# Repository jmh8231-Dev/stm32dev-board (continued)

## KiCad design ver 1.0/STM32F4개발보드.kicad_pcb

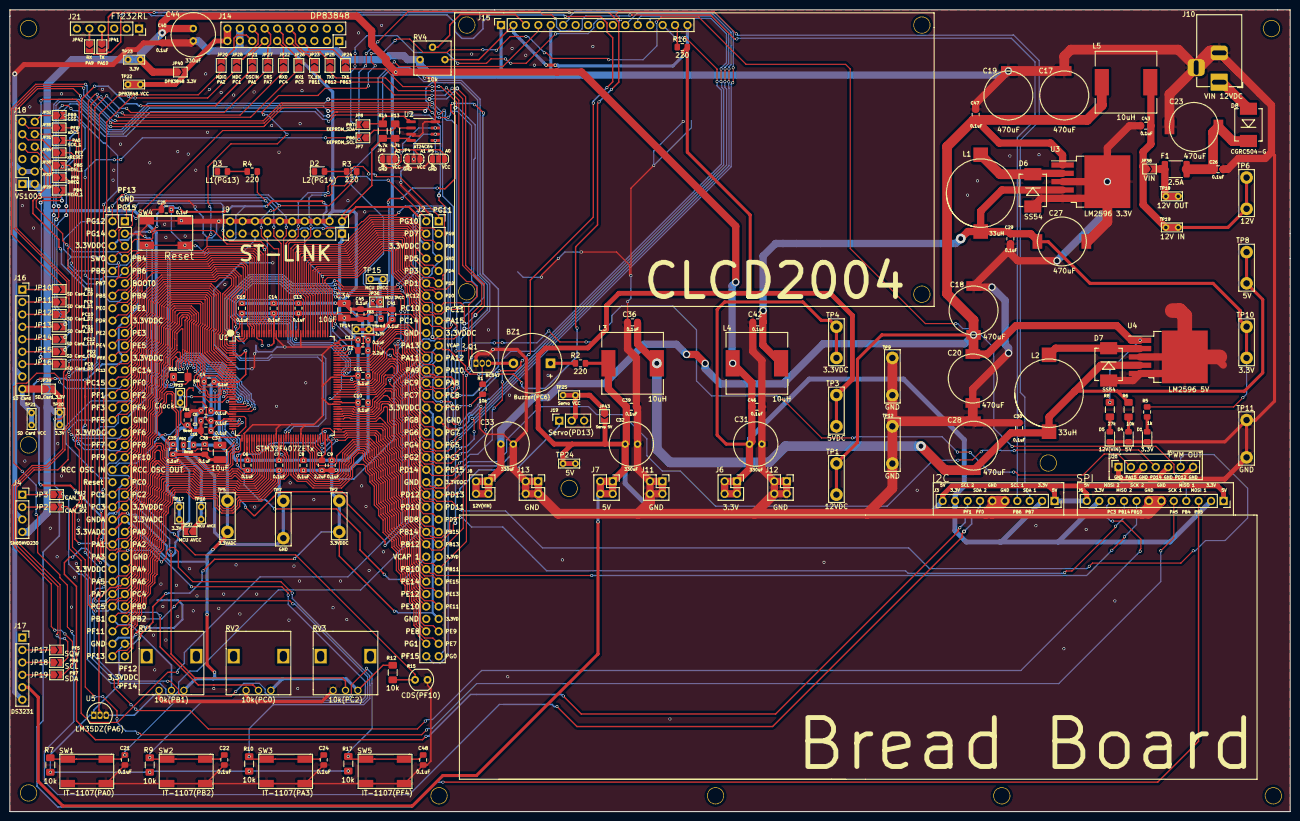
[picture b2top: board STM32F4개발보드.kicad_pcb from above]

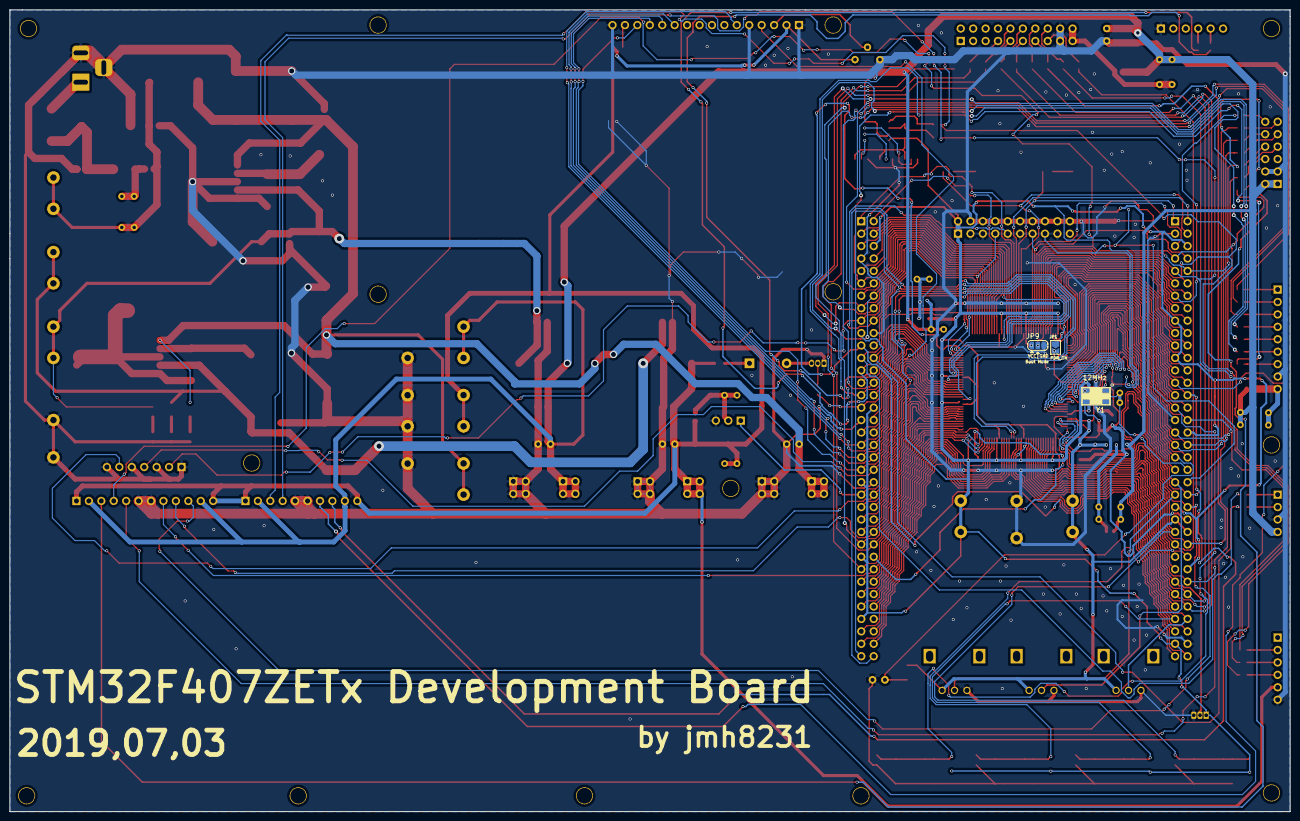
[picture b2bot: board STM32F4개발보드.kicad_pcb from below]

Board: 2 copper layers, 261.6 x 163.8 mm, 202 parts (3 on the bottom side), 182 nets.

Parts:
 : h
 #2,  #3,  #4,  #5,  #6,  #7,  #8,  #9,  #10,  #11,  #12,  #13,  #14: h
BZ1: Buzzer(PC6); Buzzer_12x9.5RM7.6
C1, C2: 2.2uF; C_0805_2012Metric_Pad1.15x1.40mm_HandSolder
C3, C4, C5, C6, C7, C8, C9, C10, C11, C12, C13, C14, C15, C16, C21, C22, C24, C25, C26, C29, C30, C35, C36, C38, C39, C40, C41, C42, C43, C45, C46, C47, C48: 0.1uF; C_0805_2012Metric_Pad1.15x1.40mm_HandSolder
C17, C18, C19, C20, C23, C27, C28: 470uF; MVG25WV470M
C31, C32, C33, C44: 330uF; c1
C34, C37: 10uF; C_1210_3225Metric_Pad1.42x2.65mm_HandSolder
D1: 3.3V; LED_0805_2012Metric_Pad1.15x1.40mm_HandSolder
D2: L2(PG14); LED_0805_2012Metric_Pad1.15x1.40mm_HandSolder
D3: L1(PG13); LED_0805_2012Metric_Pad1.15x1.40mm_HandSolder
D4: 5V; LED_0805_2012Metric_Pad1.15x1.40mm_HandSolder
D5: 12V(VIN); LED_0805_2012Metric_Pad1.15x1.40mm_HandSolder
D6, D7: SS54
D8: CGRC504-G; SS54
F1: 2.5A; Fuse_1812_4532Metric_Pad1.30x3.40mm_HandSolder
FB1, FB2, FB3: Bead; L_0805_2012Metric_Pad1.15x1.40mm_HandSolder
J1, J2: PinSocket_2x36_P2.54mm_Vertical
J3: I2C; PinSocket_1x10_P2.54mm_Vertical
J4: SN65HVD230; PinSocket_1x04_P2.54mm_Vertical
J5: SPI; PinSocket_1x12_P2.54mm_Vertical
J6: 3.3V; PinSocket_2x02_P2.54mm_Vertical
J7: 5V; PinSocket_2x02_P2.54mm_Vertical
J8: 12V(VIN); PinSocket_2x02_P2.54mm_Vertical
J9: ST-LINK; PinSocket_2x10_P2.54mm_Vertical
J10: VIN 12VDC; BarrelJack_Horizontal
J11, J12, J13: GND; PinSocket_2x02_P2.54mm_Vertical
J14: DP83848; PinSocket_2x10_P2.54mm_Vertical
J15: CLCD2004; PinSocket_1x16_P2.54mm_Vertical
J16: SD Card; PinSocket_1x09_P2.54mm_Vertical
J17: DS3231; PinSocket_1x06_P2.54mm_Vertical
J18: VS1003; PinSocket_2x06_P2.54mm_Vertical
J19: Servo(PD13); PinSocket_1x03_P2.54mm_Vertical
J20: PWM OUT; PinSocket_1x07_P2.54mm_Vertical
J21: FT232RL; PinSocket_1x06_P2.54mm_Vertical
JP1: PDR_ON; SolderJumper-2_P1.3mm_Open_TrianglePad1.0x1.5mm
JP2: CAN_RX; SolderJumper-2_P1.3mm_Open_TrianglePad1.0x1.5mm
JP3: CAN_TX; SolderJumper-2_P1.3mm_Open_TrianglePad1.0x1.5mm
JP4: A1; SolderJumper-3_P1.3mm_Open_RoundedPad1.0x1.5mm
JP5: A0; SolderJumper-3_P1.3mm_Open_RoundedPad1.0x1.5mm
JP6: A2; SolderJumper-3_P1.3mm_Open_RoundedPad1.0x1.5mm
JP7: EEPROM_SCL; SolderJumper-2_P1.3mm_Open_TrianglePad1.0x1.5mm
JP8: EEPROM_SDA; SolderJumper-2_P1.3mm_Open_TrianglePad1.0x1.5mm
JP9: Boot Mode; SolderJumper-3_P1.3mm_Open_RoundedPad1.0x1.5mm
JP10: SD Card_CD; SolderJumper-2_P1.3mm_Open_TrianglePad1.0x1.5mm
JP11: SD Card_D1; SolderJumper-2_P1.3mm_Open_TrianglePad1.0x1.5mm
JP12: SD Card_D2; SolderJumper-2_P1.3mm_Open_TrianglePad1.0x1.5mm
JP13: SD Card_D3; SolderJumper-2_P1.3mm_Open_TrianglePad1.0x1.5mm
JP14: SD Card_CLK; SolderJumper-2_P1.3mm_Open_TrianglePad1.0x1.5mm
JP15: SD Card_CMD; SolderJumper-2_P1.3mm_Open_TrianglePad1.0x1.5mm
JP16: SD Card_D0; SolderJumper-2_P1.3mm_Open_TrianglePad1.0x1.5mm
JP17: SQW; SolderJumper-2_P1.3mm_Open_TrianglePad1.0x1.5mm
JP18: SCL; SolderJumper-2_P1.3mm_Open_TrianglePad1.0x1.5mm
JP19: SDA; SolderJumper-2_P1.3mm_Open_TrianglePad1.0x1.5mm
JP20: MDIO; SolderJumper-2_P1.3mm_Open_TrianglePad1.0x1.5mm
JP21: OSCIN; SolderJumper-2_P1.3mm_Open_TrianglePad1.0x1.5mm
JP22: RX0; SolderJumper-2_P1.3mm_Open_TrianglePad1.0x1.5mm
JP23: TX_EN; SolderJumper-2_P1.3mm_Open_TrianglePad1.0x1.5mm
JP24: TX1; SolderJumper-2_P1.3mm_Open_TrianglePad1.0x1.5mm
JP25: TX0; SolderJumper-2_P1.3mm_Open_TrianglePad1.0x1.5mm
JP26: RX1; SolderJumper-2_P1.3mm_Open_TrianglePad1.0x1.5mm
JP27: CRS; SolderJumper-2_P1.3mm_Open_TrianglePad1.0x1.5mm
JP28: MDC; SolderJumper-2_P1.3mm_Open_TrianglePad1.0x1.5mm
JP29: MISO_1; SolderJumper-2_P1.3mm_Open_TrianglePad1.0x1.5mm
JP30: MOSI_1; SolderJumper-2_P1.3mm_Open_TrianglePad1.0x1.5mm
JP31: SCK_1; SolderJumper-2_P1.3mm_Open_TrianglePad1.0x1.5mm
JP32: CSS; SolderJumper-2_P1.3mm_Open_TrianglePad1.0x1.5mm
JP33: DREQ; SolderJumper-2_P1.3mm_Open_TrianglePad1.0x1.5mm
JP34: xRESET; SolderJumper-2_P1.3mm_Open_TrianglePad1.0x1.5mm
JP35: xDCS; SolderJumper-2_P1.3mm_Open_TrianglePad1.0x1.5mm
JP36: MCU DVCC; SolderJumper-2_P1.3mm_Open_TrianglePad1.0x1.5mm
JP37: MCU AVCC; SolderJumper-2_P1.3mm_Open_TrianglePad1.0x1.5mm
JP38: VIN; SolderJumper-2_P1.3mm_Open_TrianglePad1.0x1.5mm
JP39: SD_Card_3.3V; SolderJumper-2_P1.3mm_Open_TrianglePad1.0x1.5mm
JP40: DP83848 3.3V; SolderJumper-2_P1.3mm_Open_TrianglePad1.0x1.5mm
JP41: TX; SolderJumper-2_P1.3mm_Open_TrianglePad1.0x1.5mm
JP42: RX; SolderJumper-2_P1.3mm_Open_TrianglePad1.0x1.5mm
JP43: Servo 5V; SolderJumper-2_P1.3mm_Open_TrianglePad1.0x1.5mm
L1, L2: 33uH; SRR1806-330M
L3, L4, L5: 10uH; L_12x12mm_H6mm
Q1: BC547; TO-92_Inline
R1: 10k; R_0805_2012Metric_Pad1.15x1.40mm_HandSolder
R2, R3, R4, R16: 220; R_0805_2012Metric_Pad1.15x1.40mm_HandSolder
R5: 1k; R_0805_2012Metric_Pad1.15x1.40mm_HandSolder
R6, R7, R9, R10, R11, R12, R17: 10k; R_1206_3216Metric_Pad1.42x1.75mm_HandSolder
R8: 27k; R_1206_3216Metric_Pad1.42x1.75mm_HandSolder
R13, R14: 4.7k; R_1206_3216Metric_Pad1.42x1.75mm_HandSolder
R15: CDS(PF10); R_LDR_4.9x4.2mm_P2.54mm_Vertical
RV1: 10k(PB1); RV09H20SQ-B10K
RV2: 10k(PC0); RV09H20SQ-B10K
RV3: 10k(PC2); RV09H20SQ-B10K
RV4: 10k; 3362P-103LF
SW1: IT-1107(PA0); SW_SMD_IT-1107
SW2: IT-1107(PB2); SW_SMD_IT-1107
SW3: IT-1107(PA3); SW_SMD_IT-1107
SW4: Reset; SW_SMD_IT-1107
SW5: IT-1107(PF4); SW_SMD_IT-1107
TP1: 12VDC; TestPoint_Bridge_Pitch6.35mm_Drill1.3mm
TP2: 3.3VDDC; TestPoint_Bridge_Pitch6.35mm_Drill1.3mm
TP3: 5VDC; TestPoint_Bridge_Pitch6.35mm_Drill1.3mm
TP4: 3.3VDC; TestPoint_Bridge_Pitch6.35mm_Drill1.3mm
TP5: 3.3VADC; TestPoint_Bridge_Pitch6.35mm_Drill1.3mm
TP6: 12V; TestPoint_Bridge_Pitch6.35mm_Drill1.3mm
TP7, TP9, TP11, TP12: GND; TestPoint_Bridge_Pitch7.62mm_Drill1.3mm
TP8: 5V; TestPoint_Bridge_Pitch6.35mm_Drill1.3mm
TP10: 3.3V; TestPoint_Bridge_Pitch6.35mm_Drill1.3mm
TP13: Clock; TestPoint_Bridge_Pitch2.0mm_Drill0.7mm
TP14, TP17, TP20, TP23: 3.3V; TestPoint_Bridge_Pitch2.54mm_Drill0.7mm
TP15: MCU DVCC; TestPoint_Bridge_Pitch2.54mm_Drill0.7mm
TP16: MCU AVCC; TestPoint_Bridge_Pitch2.54mm_Drill0.7mm
TP18: 12V OUT; TestPoint_Bridge_Pitch2.54mm_Drill0.7mm
TP19: 12V IN; TestPoint_Bridge_Pitch2.54mm_Drill0.7mm
TP21: SD Card VCC; TestPoint_Bridge_Pitch2.54mm_Drill0.7mm
TP22: DP83848 VCC; TestPoint_Bridge_Pitch2.54mm_Drill0.7mm
TP24: 5V; TestPoint_Bridge_Pitch2.54mm_Drill0.7mm
TP25: Servo VCC; TestPoint_Bridge_Pitch2.54mm_Drill0.7mm
U1: STM32F407ZETx; LQFP-144_20x20mm_P0.5mm
U2: AT24C64; SOIC-8_3.9x4.9mm_P1.27mm
U3: LM2596 3.3V; TO-263-5_TabPin3
U4: LM2596 5V; TO-263-5_TabPin3
U5: LM35DZ(PA6); TO-92L_Inline
Y1: 12MHz; FT5HNBPK12.0-T1

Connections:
3.3VADC: C3.1, C16.2, C37.1, C38.1, FB2.1, J1.49, J1.52, R12.2, RV1.3, RV2.3, RV3.3, TP5.1, U1.32, U1.33, Y1.4
3.3VDDC: C4.2, C5.2, C6.2, C7.2, C8.2, C9.2, C10.2, C11.2, C12.2, C13.2, C14.2, C15.2, C34.1, C45.1, FB3.1, J1.6, J1.17, J1.18, J1.23, J1.36, J1.47, J1.58, J1.69, J2.6, J2.19, J2.32, J2.43, J2.55, J2.65, J9.1, J9.2, JP1.2, JP4.3, JP5.3, JP6.3, JP9.1, R7.1, R9.1, R10.1, R11.1, R13.2, R14.2, R17.1, TP2.1, U1.6, U1.17, U1.30, U1.39, U1.52, U1.62, U1.72, U1.84, U1.95, U1.108, U1.121, U1.131, U1.143, U1.144, U2.8, U5.1
3.3VOUT: C31.2, C35.1, C40.2, C41.1, C44.2, C46.1, J3.2, J3.9, J4.4, J5.2, J5.11, J6.1, J6.2, J6.3, J6.4, J18.1, J18.2, JP36.2, JP37.2, JP39.2, JP40.1, L4.2, TP4.1, TP14.1, TP17.1, TP20.1, TP23.1
5VOUT: C32.1, C39.1, J3.1, J3.10, J5.1, J5.12, J7.1, J7.2, J7.3, J7.4, J15.2, J17.5, JP43.2, L3.2, R2.2, R16.2, RV4.3, TP3.1, TP24.1
12V: F1.1, JP38.2, TP18.1
12VOUT: C17.1, C18.1, C19.1, C20.1, C33.1, C47.1, J8.1, J8.2, J8.3, J8.4, L5.2, R8.2, TP1.1, U3.1, U4.1
+3V3: C27.1, C29.1, C42.1, L1.2, L4.1, R5.2, TP10.1, U3.4
+5V: C28.1, C30.1, C36.1, L2.2, L3.1, R6.2, TP8.1, U4.4
+12V: C43.1, JP38.1, L5.1, TP6.1, TP19.1
A: J15.15, R16.1
A0: JP5.2, U2.1
A1: JP4.2, U2.2
A2: JP6.2, U2.3
BOOT0: J1.11, JP9.2, U1.138
CD: J16.1, JP10.1
CLK: J16.5, JP14.1
CMD: J16.6, JP15.1
CRS: J14.14, JP27.2
CRX: J4.2, JP2.1
CTX: J4.1, JP3.1
DP83848_Power: J14.19, J14.20, JP40.2, TP22.1
DREQ: J18.7, JP33.1
GND: C1.2, C2.2, C4.1, C5.1, C6.1, C7.1, C8.1, C9.1, C10.1, C11.1, C12.1, C13.1, C14.1, C15.1, C17.2, C18.2, C19.2, C20.2, C21.1, C22.1, C23.2, C24.1, C25.1, C26.2, C27.2, C28.2, C29.2, C30.2, C31.1, C32.2, C33.2, C34.2, C36.2, C39.2, C40.1, C41.2, C42.2, C43.2, C44.1, C45.2, C46.2, C47.2, C48.1, D1.1, D2.1, D3.1, D4.1, D5.1, D6.2, D7.2, FB1.2, J1.3, J1.33, J1.55, J1.70, J2.7, J2.20, J2.33, J2.44, J2.66, J3.5, J3.6, J4.3, J5.6, J5.7, J9.3, J9.5, J9.7, J9.9, J9.11, J9.13, J9.15, J9.17, J9.19, J10.2, J10.3, J11.1, J11.2, J11.3, J11.4, J12.1, J12.2, J12.3, J12.4, J13.1, J13.2, J13.3, J13.4, J14.17, J14.18, J15.1, J15.5, J15.16, J16.8, J17.6, J18.3, J18.4, J19.3, J20.1, J20.3, J20.5, J20.7, J21.1, JP4.1, JP5.1, JP6.1, JP9.3, Q1.1, R1.2, R15.2, RV1.1, RV2.1, RV3.1, RV4.1, SW1.3, SW1.4, SW2.3, SW2.4, SW3.3, SW3.4, SW4.3, SW4.4, SW5.3, SW5.4, TP7.1, TP9.1, TP11.1, TP12.1, U1.16, U1.38, U1.51, U1.61, U1.83, U1.94, U1.107, U1.120, U1.130, U2.4, U2.7, U3.3, U3.5, U4.3, U4.5, U5.3
GNDA: C3.2, C16.1, C35.2, C37.2, C38.2, FB1.1, J1.50, U1.31, Y1.1, Y1.2
MDC: J14.16, JP28.2
MDIO: J14.15, JP20.2
MISO_1: J1.7, J5.4, JP29.2, U1.134
MISO_2: J2.52, J5.9, U1.75
MOSI_1: J1.10, J5.3, JP30.2, U1.135
MOSI_2: J1.48, J5.10, U1.29
unnamed: BZ1.1, R2.1
unnamed: BZ1.2, Q1.3
unnamed: C23.1, C26.1, D8.1, F1.2
unnamed: D1.2, R5.1
unnamed: D2.2, R3.2
unnamed: D3.2, R4.2
unnamed: D4.2, R6.1
unnamed: D5.2, R8.1
unnamed: D6.1, L1.1, U3.2
unnamed: D7.1, L2.1, U4.2
unnamed: D8.2, J10.1
unnamed: FB2.2, JP37.1, TP16.1
unnamed: FB3.2, JP36.1, TP15.1
unnamed: J18.6, JP29.1
unnamed: J18.8, JP30.1
unnamed: J18.10, JP31.1
unnamed: J18.12, JP32.1
unnamed: J19.2, JP43.1, TP25.1
OSCIN: J14.13, JP21.2
PA0: C21.2, J1.51, R7.2, SW1.1, SW1.2, U1.34
PA1: J1.54, JP21.1, U1.35
PA2: J1.53, JP20.1, U1.36
PA3: C24.2, J1.56, R10.2, SW3.1, SW3.2, U1.37
PA4: J1.57, U1.40
PA5: J1.60, J5.5, JP31.2, U1.41
PA6: J1.59, U1.42, U5.2
PA7: J1.62, JP27.1, U1.43
PA8: J2.27, U1.100
PA9: J2.26, JP42.2, U1.101
PA10: J2.25, JP41.2, U1.102
PA11: J2.24, JP2.2, U1.103
PA12: J2.23, JP3.2, U1.104
PA15: J2.17, J20.2, U1.110
PB0: J1.63, U1.46
PB1: J1.66, RV1.2, U1.47
PB2: C22.2, J1.65, R9.2, SW2.1, SW2.2, U1.48
PB6: J1.9, J3.4, JP7.2, JP18.2, U1.136
PB7: J1.12, J3.3, JP8.2, JP19.2, U1.137
PB8: J1.14, U1.139
PB9: J1.13, JP32.2, U1.140
PB10: J2.58, J5.8, U1.69
PB11: J2.57, JP23.1, U1.70
PB12: J2.54, JP25.1, U1.73
PB13: J2.53, JP24.1, U1.74
PB15: J2.51, U1.76
PC0: J1.43, RV2.2, U1.26
PC1: J1.46, JP28.1, U1.27
PC2: J1.45, RV3.2, U1.28
PC4: J1.61, JP22.1, U1.44
PC5: J1.64, JP26.1, U1.45
PC6: J2.31, Q1.2, R1.1, U1.96
PC7: J2.30, U1.97
PC8: J2.29, JP16.2, U1.98
PC9: J2.28, JP11.2, U1.99
PC10: J2.16, JP12.2, U1.111
PC11: J2.15, JP13.2, U1.112
PC12: J2.14, JP14.2, U1.113
PC13: J1.26, U1.7
PC14: J1.25, U1.8
PC15: J1.28, U1.9
PD0: J2.13, U1.114
PD1: J2.12, JP10.2, U1.115
PD2: J2.11, JP15.2, U1.116
PD3: J2.10, U1.117
PD4: J2.9, U1.118
PD5: J2.8, U1.119
PD6: J2.5, U1.122
PD7: J2.4, U1.123
PD8: J2.50, U1.77
PD9: J2.49, U1.78
PD10: J2.48, U1.79
PD11: J2.47, U1.80
PD12: J2.46, J20.6, U1.81
PD13: J2.45, J19.1, U1.82
PD14: J2.42, J20.4, U1.85
PD15: J2.41, J15.14, U1.86
PE0: J1.16, U1.141
PE1: J1.15, U1.142
PE2: J1.20, U1.1
PE3: J1.19, U1.2
PE4: J1.22, U1.3
PE5: J1.21, U1.4
PE6: J1.24, U1.5
PE7: J2.69, U1.58
PE8: J2.68, U1.59
PE9: J2.67, U1.60
PE10: J2.64, U1.63
PE11: J2.63, U1.64
PE12: J2.62, U1.65
PE13: J2.61, U1.66
PE14: J2.60, U1.67
PE15: J2.59, U1.68
PF0: J1.27, J3.7, U1.10
PF1: J1.30, J3.8, U1.11
PF2: J1.29, U1.12
PF3: J1.32, U1.13
PF4: C48.2, J1.31, R17.2, SW5.1, SW5.2, U1.14
PF5: J1.34, JP17.2, U1.15
PF6: J1.35, JP33.2, U1.18
PF7: J1.38, JP34.2, U1.19
PF8: J1.37, JP35.2, U1.20
PF9: J1.40, U1.21
PF10: J1.39, R12.1, R15.1, U1.22
PF11: J1.68, U1.49
PF12: J1.67, U1.50
PF13: J1.72, U1.53
PF14: J1.71, U1.54
PF15: J2.72, U1.55
PG0: J2.71, U1.56
PG1: J2.70, U1.57
PG2: J2.40, J15.13, U1.87
PG3: J2.39, J15.12, U1.88
PG4: J2.38, J15.11, U1.89
PG5: J2.37, J15.6, U1.90
PG6: J2.36, J15.4, U1.91
PG7: J2.35, U1.92
PG8: J2.34, U1.93
PG9: J2.3, U1.124
PG10: J2.2, U1.125
PG11: J2.1, U1.126
PG12: J1.2, U1.127
PG13: J1.1, R4.1, U1.128
PG14: J1.4, R3.1, U1.129
PG15: J1.5, U1.132
RCC_OSC_IN: J1.42, TP13.1, U1.23, Y1.3
RCC_OSC_OUT: J1.41, U1.24
RX0: J14.11, JP22.2
RX1: J14.12, JP26.2
Reset: C25.2, J1.44, J9.16, R11.2, SW4.1, SW4.2, U1.25
SCL: JP7.1, R13.1, U2.6
SCL_DS: J17.3, JP18.1
SDA: JP8.1, R14.1, U2.5
SDA_DS: J17.4, JP19.1
SDIO_D0: J16.7, JP16.1
SDIO_D1: J16.2, JP11.1
SDIO_D2: J16.3, JP12.1
SDIO_D3: J16.4, JP13.1
SD_Card_Power: J16.9, JP39.1, TP21.1
SQW: J17.2, JP17.1
SWCLK: J2.18, J9.10, U1.109
SWDIO: J2.22, J9.8, U1.105
SWO: J1.8, J9.14, U1.133
TX0: J14.10, JP25.2
TX1: J14.7, JP24.2
TX_EN: J14.9, JP23.2
UART_RX: J21.5, JP42.1
UART_TX: J21.4, JP41.1
VCAP2: C2.1, J2.21, U1.106
VCAP_1: C1.1, J2.56, U1.71
VO: J15.3, RV4.2
xDCS: J18.11, JP35.1
xRESET: J18.9, JP34.1

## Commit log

2025-08-25 STM32 Dev Board HW v1.0
2025-08-25 add hw v1.0
2025-08-25 add hw v2.0
2025-08-25 add doc
